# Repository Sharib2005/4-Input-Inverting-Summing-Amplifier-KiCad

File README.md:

# 4-Input-Inverting-Summing-Amplifier-KiCad

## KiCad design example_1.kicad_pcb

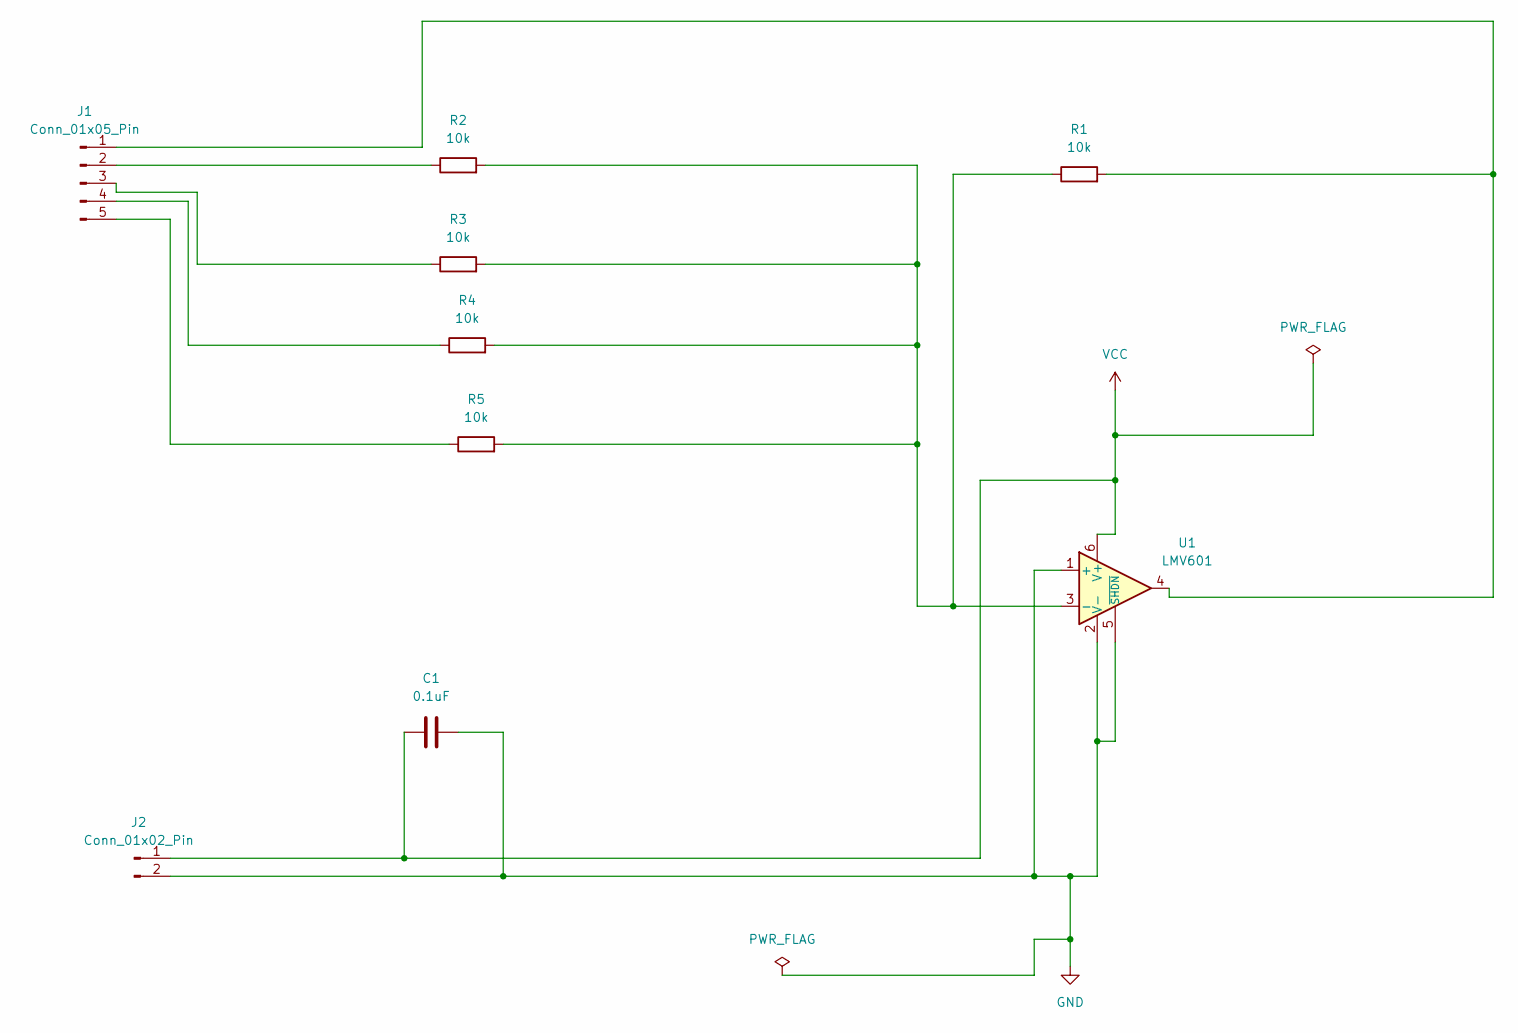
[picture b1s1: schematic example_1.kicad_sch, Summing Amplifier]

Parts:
C1: 0.1uF; C_Disc_D5.1mm_W3.2mm_P5.00mm
J1: Conn_01x05_Pin; PinHeader_1x05_P2.54mm_Vertical
J2: Conn_01x02_Pin; PinHeader_1x02_P2.54mm_Vertical
R1, R2, R3, R4, R5: 10k; R_Axial_DIN0207_L6.3mm_D2.5mm_P7.62mm_Horizontal
U1: LMV601; SOT-363_SC-70-6

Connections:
GND: C1.2, J2.2, U1.1 (+), U1.2 (V-), U1.5 (~SHDN)
unnamed: J1.1, R1.2, U1.4
unnamed: J1.2, R2.1
unnamed: J1.3, R3.1
unnamed: J1.4, R4.1
unnamed: J1.5, R5.1
unnamed: R1.1, R2.2, R3.2, R4.2, R5.2, U1.3 (-)
VCC: C1.1, J2.1, U1.6 (V+)

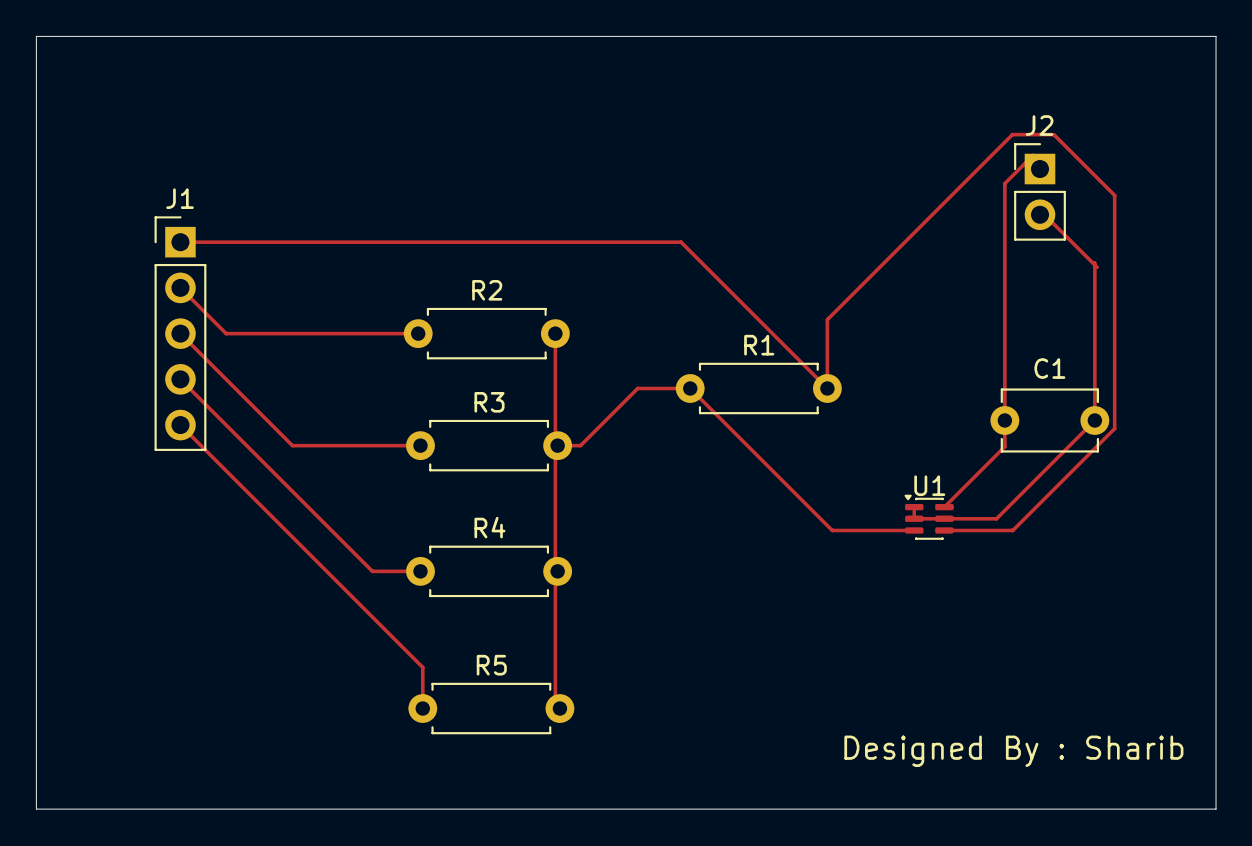
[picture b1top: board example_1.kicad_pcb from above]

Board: 2 copper layers, 65.5 x 42.9 mm, 9 parts (0 on the bottom side), 8 nets.
